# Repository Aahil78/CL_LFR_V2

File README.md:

# Cyber Link's LFR V2

This bot is Cyber Link's Line Follower V2 (Originally named L2-B2)

# Features
- The PCB is the chassis
- It's compact
- It uses the ESP32-S3, QTR-8RC, TB6612FNG, IP2721 PD Sink IC, etc.
- It has holes to mount two N20 Micro gear motors
- It is high speed and has pads to add 3x Li-ion batteries or holders.
- And more!

# More to come soon!

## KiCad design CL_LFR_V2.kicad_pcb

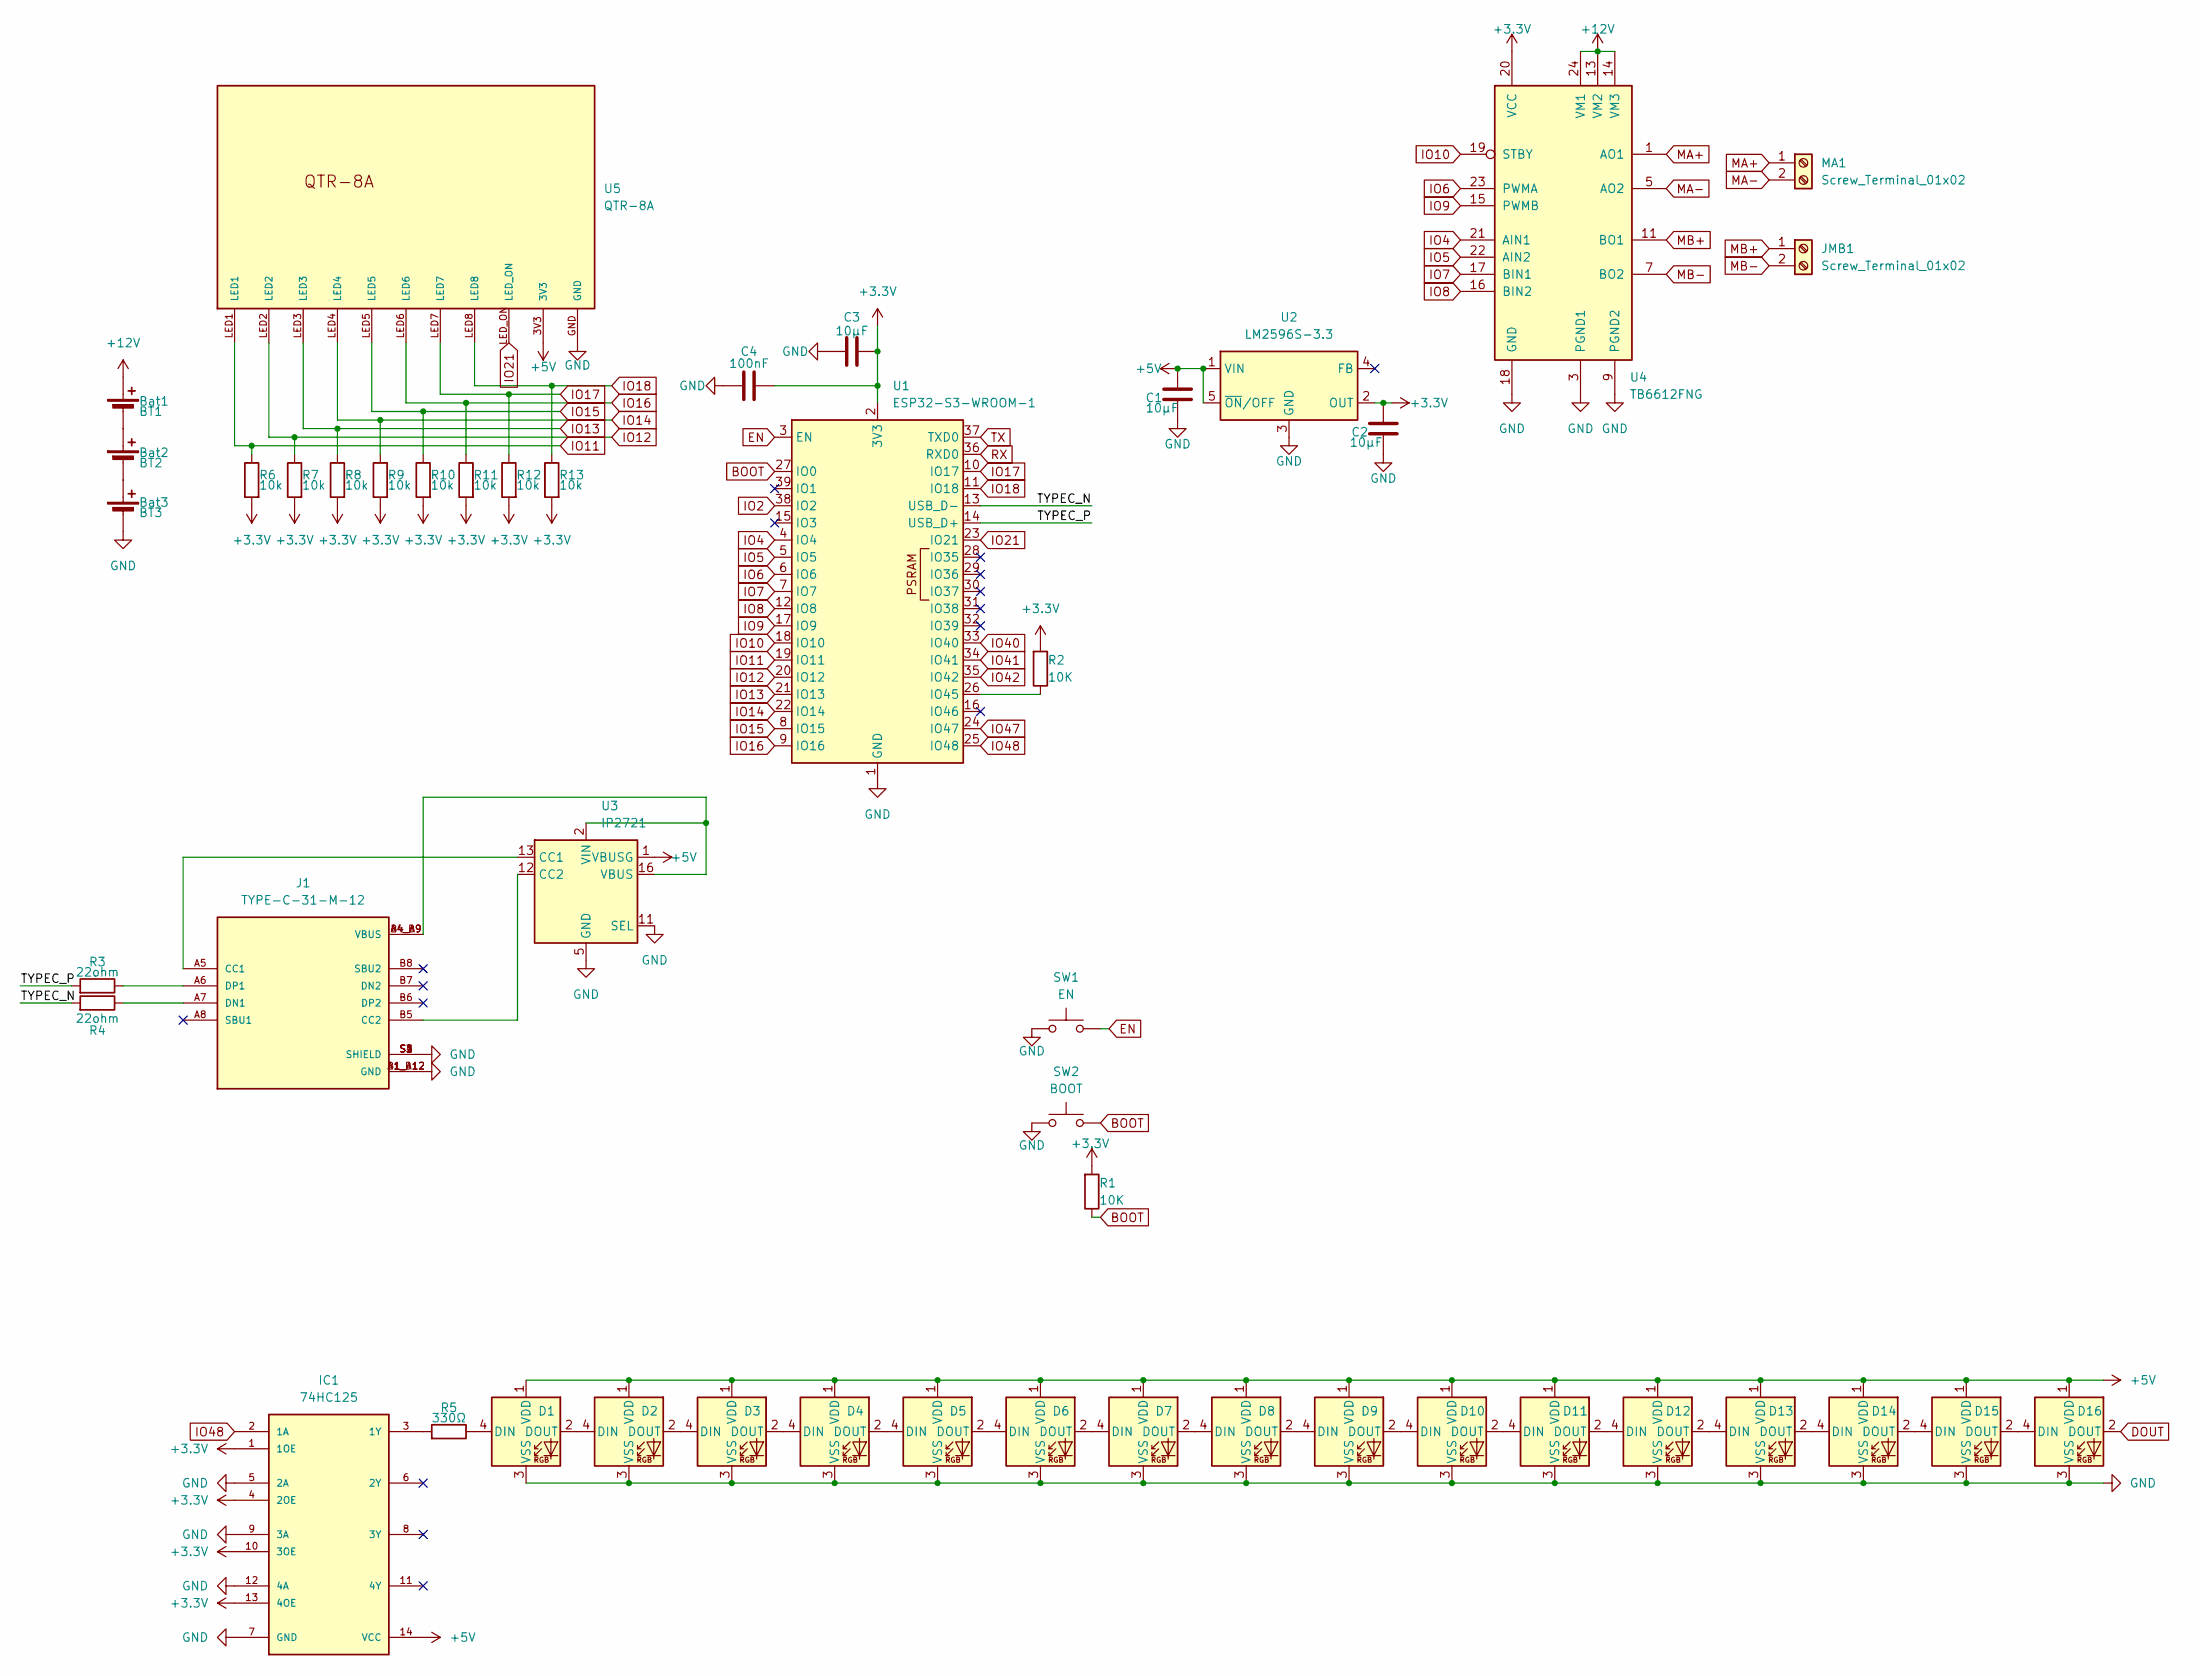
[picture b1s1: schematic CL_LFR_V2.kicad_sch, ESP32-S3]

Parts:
BT1: Bat1; BatteryHolder_MPD_BH-18650-PC2
BT2: Bat2; BatteryHolder_MPD_BH-18650-PC2
BT3: Bat3; BatteryHolder_MPD_BH-18650-PC2
C1, C2, C3: 10µF; C_0805_2012Metric
C4: 100nF; C_0402_1005Metric
D1, D2, D3, D4, D5, D6, D7, D8, D9, D10, D11, D12, D13, D14, D15, D16: SK6812MINI; SK6812-MINI-E
IC1: 74HC125; SOIC-14
J1: TYPE-C-31-M-12; HRO_TYPE-C-31-M-12; PARTREV 2020.12.08
JMB1: Screw_Terminal_01x02; JST_EH_B2B-EH-A_1x02_P2.50mm_Vertical
MA1: Screw_Terminal_01x02; JST_EH_B2B-EH-A_1x02_P2.50mm_Vertical
R1, R2: 10K; R_0402_1005Metric
R3, R4: 22ohm; R_0402_1005Metric
R5: 330Ω; R_0805_2012Metric
R6, R7, R8, R9, R10, R11, R12, R13: 10k; R_0805_2012Metric
SW1: EN; SW_Tactile_SPST_NO_Straight_CK_PTS636Sx25SMTRLFS
SW2: BOOT; SW_Tactile_SPST_NO_Straight_CK_PTS636Sx25SMTRLFS
U1: ESP32-S3-WROOM-1
U2: LM2596S-3.3; TO-263-5_TabPin3
U3: IP2721; TSSOP-16_4.4x5mm_P0.65mm
U4: TB6612FNG; SSOP-24_5.3x8.2mm_P0.65mm
U5: QTR-8A

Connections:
+3.3V: C2.1, C3.2, C4.2, IC1.1 (1OE), IC1.4 (2OE), IC1.10 (3OE), IC1.13 (4OE), R1.1, R2.1, R6.1, R7.1, R8.1, R9.1, R10.1, R11.1, R12.1, R13.1, U1.2 (3V3), U2.2 (OUT), U4.20 (VCC)
+5V: C1.1, D1.1 (VDD), D2.1 (VDD), D3.1 (VDD), D4.1 (VDD), D5.1 (VDD), D6.1 (VDD), D7.1 (VDD), D8.1 (VDD), D9.1 (VDD), D10.1 (VDD), D11.1 (VDD), D12.1 (VDD), D13.1 (VDD), D14.1 (VDD), D15.1 (VDD), D16.1 (VDD), IC1.14 (VCC), U2.1 (VIN), U2.5 (~ON/OFF), U3.1 (VBUSG), U5.3V3
+12V: BT1.1 (+), U4.13 (VM2), U4.14 (VM3), U4.24 (VM1)
/TYPEC_N: R4.1, U1.13 (USB_D-)
/TYPEC_P: R3.1, U1.14 (USB_D+)
BOOT: R1.2, SW2.2, U1.27 (IO0)
DOUT: D16.2 (DOUT)
EN: SW1.2, U1.3 (EN)
GND: BT3.2 (-), C1.2, C2.2, C3.1, C4.1, D1.3 (VSS), D2.3 (VSS), D3.3 (VSS), D4.3 (VSS), D5.3 (VSS), D6.3 (VSS), D7.3 (VSS), D8.3 (VSS), D9.3 (VSS), D10.3 (VSS), D11.3 (VSS), D12.3 (VSS), D13.3 (VSS), D14.3 (VSS), D15.3 (VSS), D16.3 (VSS), IC1.5 (2A), IC1.7 (GND), IC1.9 (3A), IC1.12 (4A), J1.A1_B12 (GND), J1.B1_A12 (GND), J1.S1 (SHIELD), J1.S2 (SHIELD), J1.S3 (SHIELD), J1.S4 (SHIELD), SW1.1, SW2.1, U1.1 (GND), U1.40 (GND), U1.41 (GND), U2.3 (GND), U3.5 (GND), U3.11 (SEL), U4.3 (PGND1), U4.4 (PGND1), U4.9 (PGND2), U4.10 (PGND2), U4.18 (GND), U5.GND
IO2: U1.38 (IO2)
IO4: U1.4 (IO4), U4.21 (AIN1)
IO5: U1.5 (IO5), U4.22 (AIN2)
IO6: U1.6 (IO6), U4.23 (PWMA)
IO7: U1.7 (IO7), U4.17 (BIN1)
IO8: U1.12 (IO8), U4.16 (BIN2)
IO9: U1.17 (IO9), U4.15 (PWMB)
IO10: U1.18 (IO10), U4.19 (STBY)
IO11: R6.2, U1.19 (IO11), U5.LED1
IO12: R7.2, U1.20 (IO12), U5.LED2
IO13: R8.2, U1.21 (IO13), U5.LED3
IO14: R9.2, U1.22 (IO14), U5.LED4
IO15: R10.2, U1.8 (IO15), U5.LED5
IO16: R11.2, U1.9 (IO16), U5.LED6
IO17: R12.2, U1.10 (IO17), U5.LED7
IO18: R13.2, U1.11 (IO18), U5.LED8
IO21: U1.23 (IO21), U5.LED_ON
IO40: U1.33 (IO40)
IO41: U1.34 (IO41)
IO42: U1.35 (IO42)
IO47: U1.24 (IO47)
IO48: IC1.2 (1A), U1.25 (IO48)
MA+: MA1.1, U4.1 (AO1), U4.2 (AO1)
MA-: MA1.2, U4.5 (AO2), U4.6 (AO2)
MB+: JMB1.1, U4.11 (BO1), U4.12 (BO1); also elsewhere on the board
MB-: JMB1.2, U4.7 (BO2), U4.8 (BO2); also elsewhere on the board
unnamed: BT1.2 (-), BT2.1 (+)
unnamed: BT2.2 (-), BT3.1 (+)
unnamed: D1.2 (DOUT), D2.4 (DIN)
unnamed: D2.2 (DOUT), D3.4 (DIN)
unnamed: D3.2 (DOUT), D4.4 (DIN)
unnamed: D4.2 (DOUT), D5.4 (DIN)
unnamed: D5.2 (DOUT), D6.4 (DIN)
unnamed: D6.2 (DOUT), D7.4 (DIN)
unnamed: D7.2 (DOUT), D8.4 (DIN)
unnamed: D8.2 (DOUT), D9.4 (DIN)
unnamed: D9.2 (DOUT), D10.4 (DIN)
unnamed: D10.2 (DOUT), D11.4 (DIN)
unnamed: D11.2 (DOUT), D12.4 (DIN)
unnamed: D12.2 (DOUT), D13.4 (DIN)
unnamed: D13.2 (DOUT), D14.4 (DIN)
unnamed: D14.2 (DOUT), D15.4 (DIN)
unnamed: D15.2 (DOUT), D16.4 (DIN)
unnamed: IC1.3 (1Y), R5.1
unnamed: J1.A5 (CC1), U3.13 (CC1)
unnamed: J1.B5 (CC2), U3.12 (CC2)
unnamed: J1.A7 (DN1), R4.2
unnamed: J1.A6 (DP1), R3.2
unnamed: R2.2, U1.26 (IO45)
unnamed: J1.A4_B9 (VBUS), J1.B4_A9 (VBUS), U3.2 (VIN), U3.16 (VBUS)
RX: U1.36 (RXD0)
TX: U1.37 (TXD0)

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
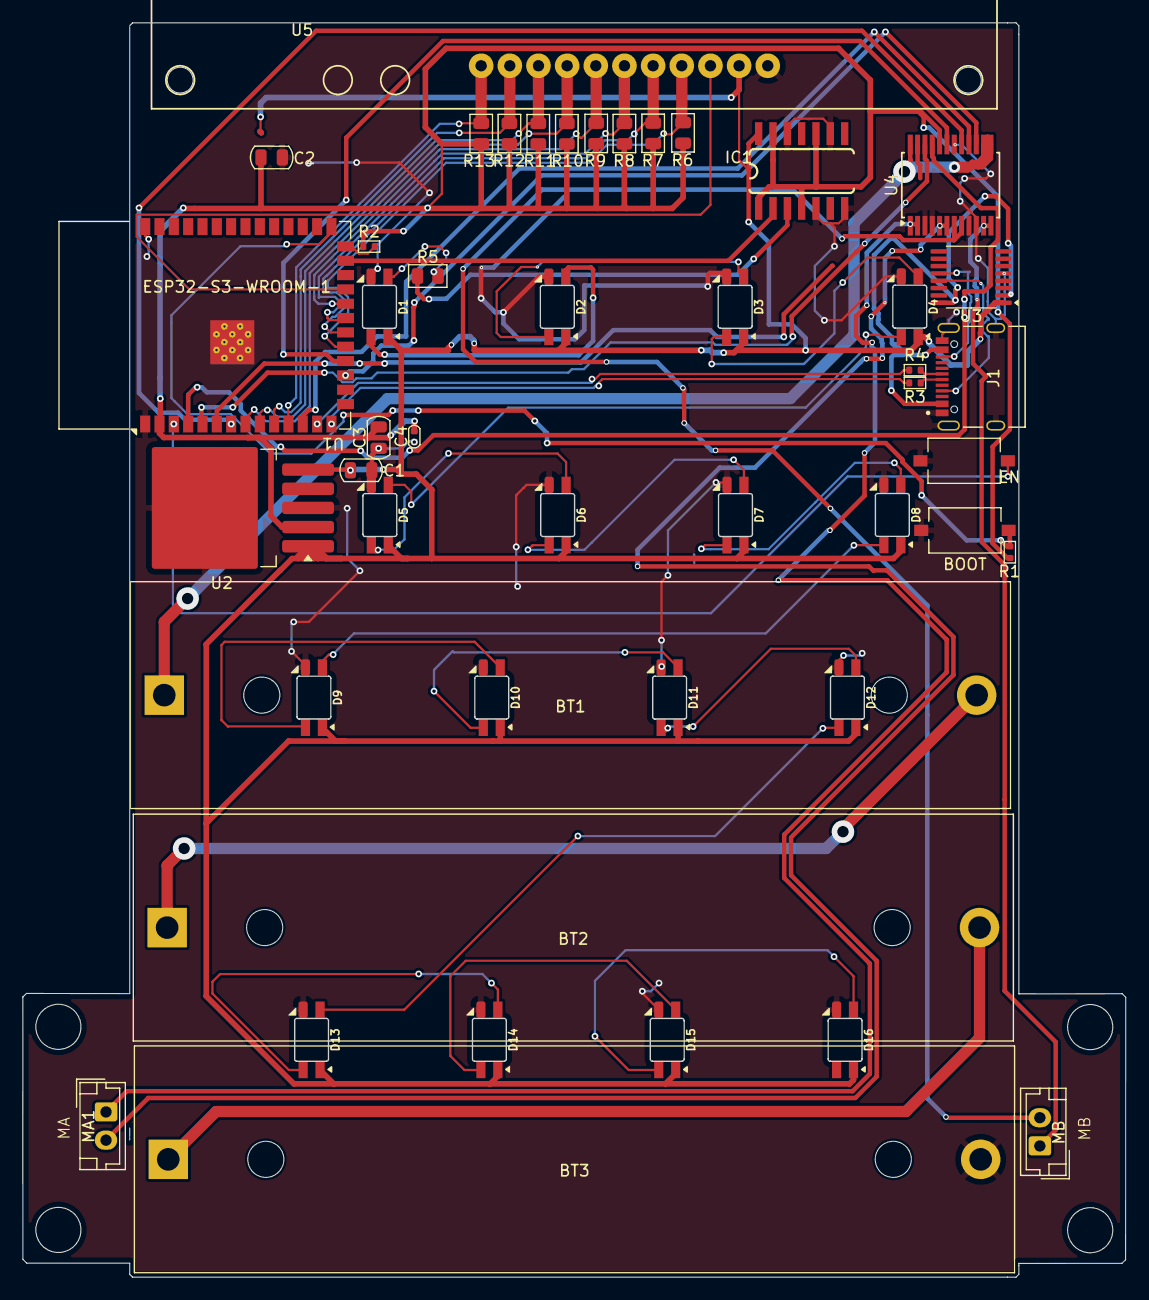
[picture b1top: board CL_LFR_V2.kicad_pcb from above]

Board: 2 copper layers, 97.7 x 111.1 mm, 49 parts (1 on the bottom side), 53 nets.

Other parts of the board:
MA: N20 Motor Bracket; N20 Bracket
MB: Screw_Terminal_01x02; JST_EH_B2B-EH-A_1x02_P2.50mm_Vertical
MB#2: N20 Motor Bracket; N20 Bracket

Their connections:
MB+: MB.1; also elsewhere on the board
MB-: MB.2; also elsewhere on the board

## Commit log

2025-05-05 Create README.md and add descriptiom
2025-05-08 Add design files
